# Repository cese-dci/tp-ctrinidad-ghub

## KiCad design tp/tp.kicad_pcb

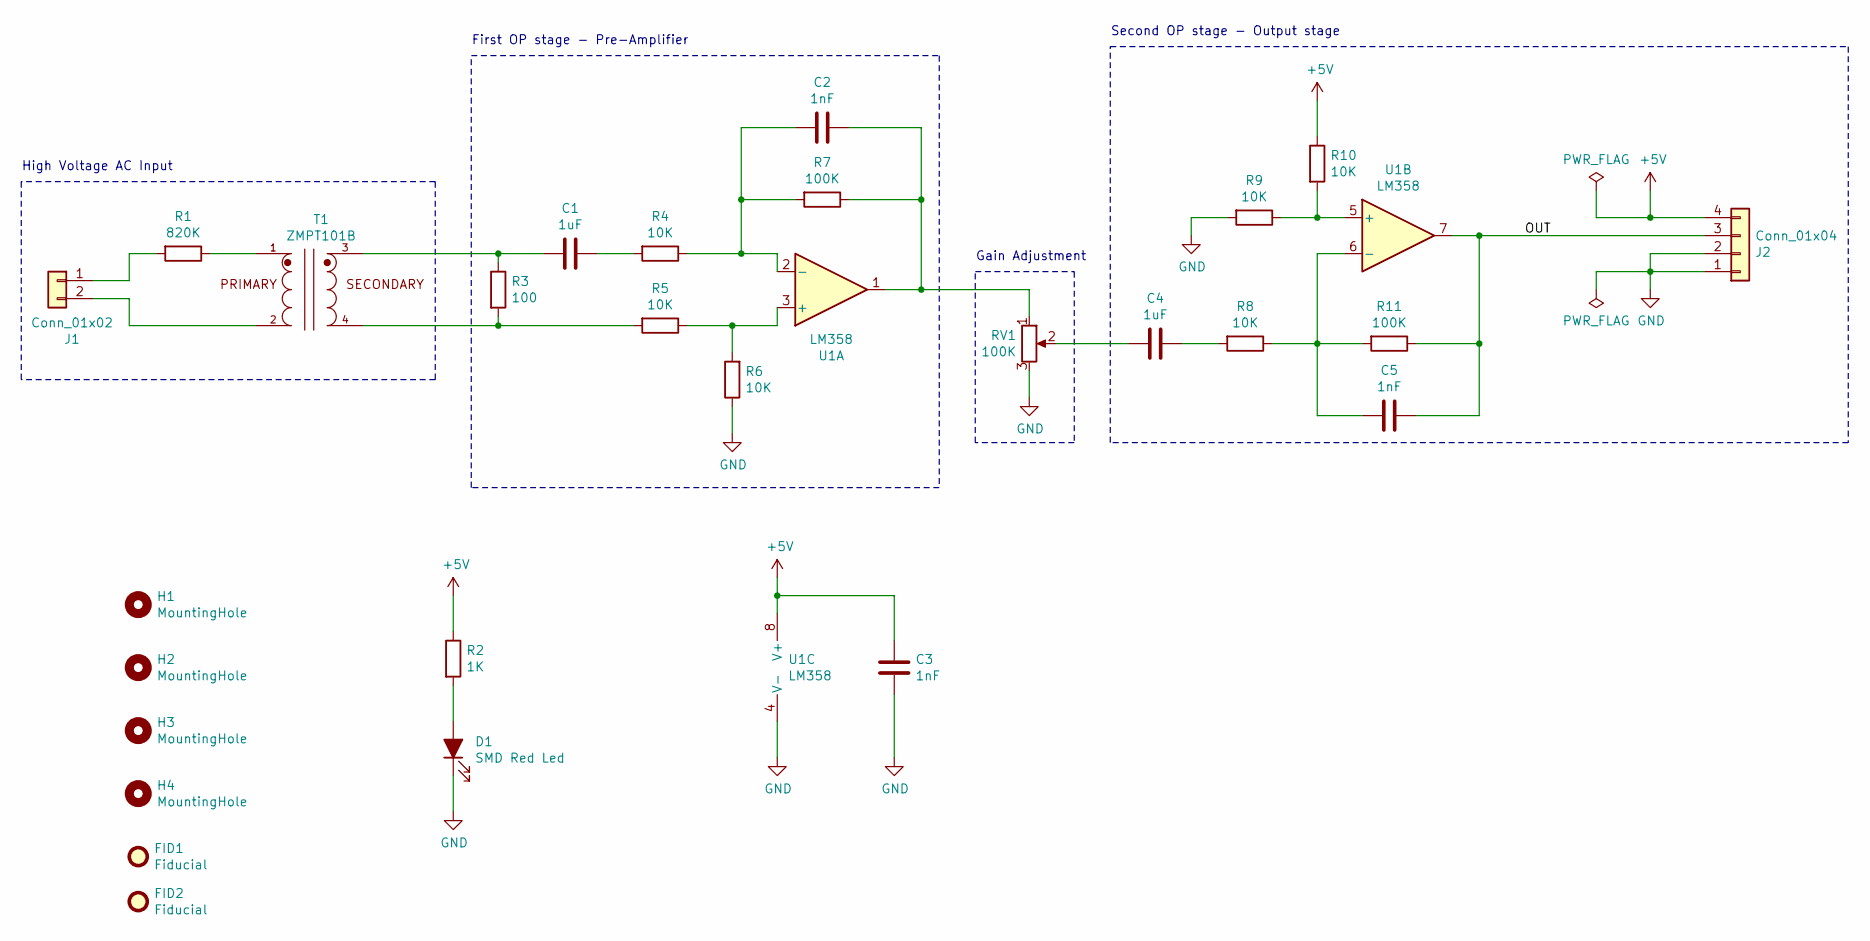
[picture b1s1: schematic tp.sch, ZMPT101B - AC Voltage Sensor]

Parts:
C1, C4: 1uF; C_0805_2012Metric
C2, C3, C5: 1nF; C_0805_2012Metric
D1: SMD Red Led; LED_1206_3216Metric; Digikey# 1830-1092-2-ND
FID1, FID2: Fiducial; Fiducial_0.5mm_Mask1.5mm
H1, H2, H3, H4: MountingHole; MountingHole_2.1mm
J1: Conn_01x02; TerminalBlock_Phoenix_MKDS-1,5-2-5.08_1x02_P5.08mm_Horizont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; Digikey# 277-5893-ND
J2: Conn_01x04; PinHeader_1x04_P2.54mm_Vertical
R1: 820K; R_0805_2012Metric
R2: 1K; R_0805_2012Metric
R3: 100; R_0805_2012Metric
R4, R5, R6, R8, R9, R10: 10K; R_0805_2012Metric
R7, R11: 100K; R_0805_2012Metric
RV1: 100K; Potentiometer_Bourns_3296W_Vertical; Digikey# 3296W-104LF-ND
T1: ZMPT101B; XFMR_ZMPT101B; Digikey# N/A
U1: LM358; SOIC-8_3.9x4.9mm_P1.27mm; Digikey# LM358AMXTR-ND

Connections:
+5V: C3.1, J2.4, R2.1, R10.1, U1.8 (V+)
/OUT: C5.1, J2.3, R11.1, U1.7
GND: C3.2, D1.1 (K), J2.1, J2.2, R6.1, R9.2, RV1.3, U1.4 (V-)
unnamed: C1.1, R4.2
unnamed: C1.2, R3.1, T1.3
unnamed: C2.1, R7.1, RV1.1, U1.1
unnamed: C2.2, R4.1, R7.2, U1.2 (-)
unnamed: C4.1, R8.2
unnamed: C4.2, RV1.2
unnamed: C5.2, R8.1, R11.2, U1.6 (-)
unnamed: D1.2 (A), R2.2
unnamed: J1.1, R1.2
unnamed: J1.2, T1.2
unnamed: R1.1, T1.1
unnamed: R3.2, R5.2, T1.4
unnamed: R5.1, R6.2, U1.3 (+)
unnamed: R9.1, R10.2, U1.5 (+)

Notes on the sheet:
High Voltage AC Input
Gain Adjustment
First OP stage - Pre-Amplifier
Second OP stage - Output stage

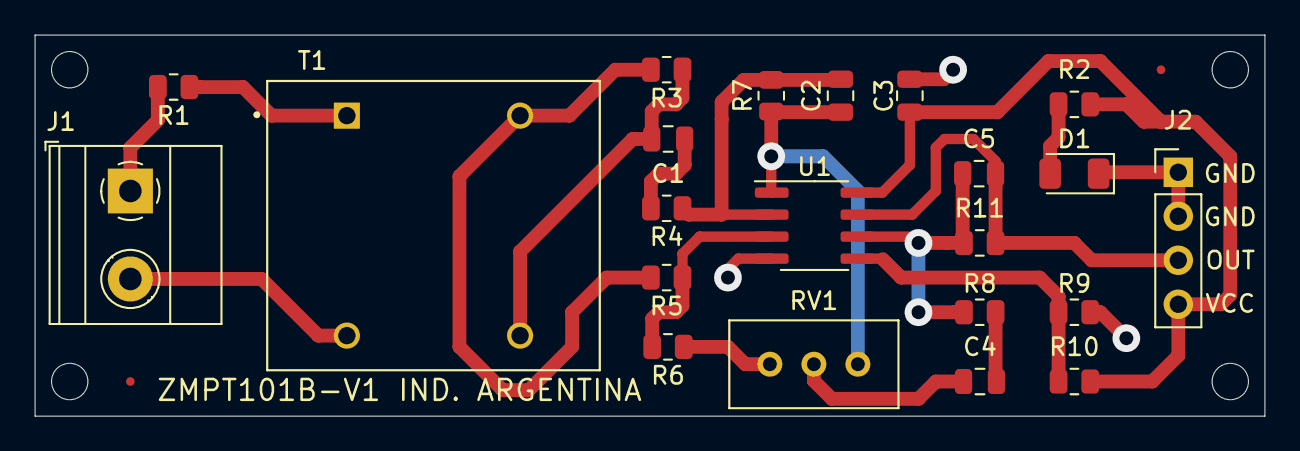
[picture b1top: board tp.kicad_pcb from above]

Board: 2 copper layers, 71.0 x 22.0 mm, 28 parts (0 on the bottom side), 17 nets.

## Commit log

2021-03-21 Esquematico primera version
2021-03-28 Agregado de: footprints, descripcion y fabricante
2021-04-07 Se agrego/arreglo segun revision de Felipe
2021-04-08 Posicionamiento de componentes en PCB
2021-04-09 Avance de PCB. Agregado de agujeros de fijacion
2021-04-15 Se aplicaron todos los comentarios hechos en la revisión del docente
2021-04-16 PCB Finalizado
2021-04-19 Proyecto actualizado según revisión F. Calcavecchia 18/04/2021
2021-04-21 Actualizado segun revision PCB docente

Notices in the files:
tp/tp.kicad_pcb:
https://creativecommons.org/license/by-sa/4.0/)
Released under the Creative Commons Attribution Share-Alike 4.0 Licence
